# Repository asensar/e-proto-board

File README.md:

# e-proto-board
Electronics Prototyping Board Inspired by Bread Board

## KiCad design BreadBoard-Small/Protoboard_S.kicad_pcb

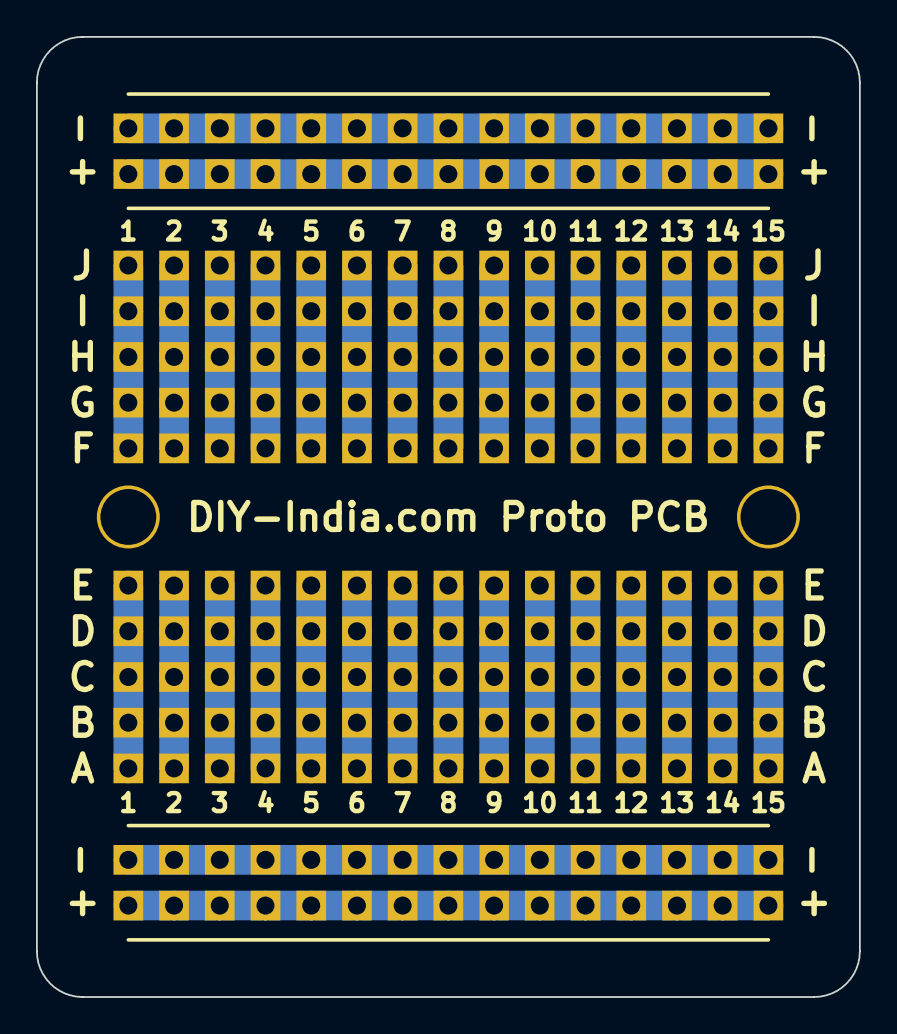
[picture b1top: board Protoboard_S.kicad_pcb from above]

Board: 2 copper layers, 45.7 x 53.3 mm, 14 parts (0 on the bottom side), 34 nets.

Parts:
P1, P2, P3, P4, P5, P6, P7, P8, P9, P10, P11, P12, P13, P14: CONN_01X15; BreadBoard_15Pin

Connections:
unnamed: P1.1, P1.2, P1.3, P1.4, P1.5, P1.6, P1.7, P1.8, P1.9, P1.10, P1.11, P1.12, P1.13, P1.14, P1.15
unnamed: P2.1, P2.2, P2.3, P2.4, P2.5, P2.6, P2.7, P2.8, P2.9, P2.10, P2.11, P2.12, P2.13, P2.14, P2.15
unnamed: P3.1, P4.1, P5.1, P6.1, P7.1
unnamed: P3.2, P4.2, P5.2, P6.2, P7.2
unnamed: P3.3, P4.3, P5.3, P6.3, P7.3
unnamed: P3.4, P4.4, P5.4, P6.4, P7.4
unnamed: P3.5, P4.5, P5.5, P6.5, P7.5
unnamed: P3.6, P4.6, P5.6, P6.6, P7.6
unnamed: P3.7, P4.7, P5.7, P6.7, P7.7
unnamed: P3.8, P4.8, P5.8, P6.8, P7.8
unnamed: P3.9, P4.9, P5.9, P6.9, P7.9
unnamed: P3.10, P4.10, P5.10, P6.10, P7.10
unnamed: P3.11, P4.11, P5.11, P6.11, P7.11
unnamed: P3.12, P4.12, P5.12, P6.12, P7.12
unnamed: P3.13, P4.13, P5.13, P6.13, P7.13
unnamed: P3.14, P4.14, P5.14, P6.14, P7.14
unnamed: P3.15, P4.15, P5.15, P6.15, P7.15
unnamed: P8.1, P8.2, P8.3, P8.4, P8.5, P8.6, P8.7, P8.8, P8.9, P8.10, P8.11, P8.12, P8.13, P8.14, P8.15
unnamed: P9.1, P9.2, P9.3, P9.4, P9.5, P9.6, P9.7, P9.8, P9.9, P9.10, P9.11, P9.12, P9.13, P9.14, P9.15
unnamed: P10.1, P11.1, P12.1, P13.1, P14.1
unnamed: P10.2, P11.2, P12.2, P13.2, P14.2
unnamed: P10.3, P11.3, P12.3, P13.3, P14.3
unnamed: P10.4, P11.4, P12.4, P13.4, P14.4
unnamed: P10.5, P11.5, P12.5, P13.5, P14.5
unnamed: P10.6, P11.6, P12.6, P13.6, P14.6
unnamed: P10.7, P11.7, P12.7, P13.7, P14.7
unnamed: P10.8, P11.8, P12.8, P13.8, P14.8
unnamed: P10.9, P11.9, P12.9, P13.9, P14.9
unnamed: P10.10, P11.10, P12.10, P13.10, P14.10
unnamed: P10.11, P11.11, P12.11, P13.11, P14.11
unnamed: P10.12, P11.12, P12.12, P13.12, P14.12
unnamed: P10.13, P11.13, P12.13, P13.13, P14.13
unnamed: P10.14, P11.14, P12.14, P13.14, P14.14
unnamed: P10.15, P11.15, P12.15, P13.15, P14.15

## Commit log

2016-08-20 Added KiCAD files
2016-08-20 Renamed Directory
2016-08-20 Added Image.png
2016-08-20 Update README.md with Image of proto board
